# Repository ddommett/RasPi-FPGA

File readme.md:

# RasPi_FPGA

RasPi_FPGA is a master project encapsulating all of my open source and open hardware projects that connect a FPGA (Lattice ice40HX4K and ECP5) to the Raspberry Pi 4 and Raspberry Pi 5 for real-time (relatively high-speed) data transfer via GPIO.

[Part 1](./Part1/readme.md) Raspberry Pi 4 with Lattice ice40HX4K FPGA using GPIO.

[Part 2](./Part2/readme.md) Raspberry Pi 5 with Lattice ECP5 FPGA using HDMI and CSI2.

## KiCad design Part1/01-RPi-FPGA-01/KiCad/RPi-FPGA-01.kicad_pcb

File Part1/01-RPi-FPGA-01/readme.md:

# RPi-FPGA-01

<div align="center">
  
</div>

<p>
The RPi-FPGA-01 is a fully open source (GPLv3) hardware design. It contains a Lattice ice40HX4K FPGA and a 40-pin header. It is intended to plug into a Raspberry Pi. It contains 56 I/O to the "outside" world via three headers and connects to all 28 GPIO pins of the Raspberry Pi. It is a 4-layer PCB with components on one side.

Aside from a few JMP inputs and LEDs, it is intended to be a simple board. It is just an FPGA designed to sit between a Raspberry Pi and any other circuit. The I/O lines are completely unprotected so static electricity from a human touching any of the IO could ruin the FPGA; please be careful.

(The IceZero was not ideal for my purposes. It had extra components, and GPIO lines were organized inefficiently for what I had in mind. Therefore I designed my own PCB.)
</p>

The [KiCad](https://github/ddommett/RasPi_FPGA/03-RPi-FPGA-01/KiCad) folder contains the KiCad project, schematic, and PCB layout design. 

The [gerbers](https://github/ddommett/RasPi_FPGA/03-RPi-FPGA-01/KiCad/gerbers) subfolder contains the gerber files for manufacture. 

The [production](https://github/ddommett/RasPi_FPGA/03-RPi-FPGA-01/KiCad/production) subfolder contains extra files useful for manufacture. I had [JLCPCB](https://jlcpcb.com/) manufacture the PCBs, supply the components, and assemble the board.

RPi-FPGA-01.csv contains a bill of materials for all components on the RPi-FPGA-01 that is in the correct format to upload to JLCPCB during the ordering process. 

jlcpcb-all-cpl.csv contains a list of positions and rotations for all components, uploadable to JLCPCB during their ordering process that enables their pick-and-place machine to perform the assembly.

## License
The RPi-FPGA-01 is an open source project licensed under GPLv3.  Please see the included LICENSE file for details.  If you do wish to distribute boards derived from this open source hardware project then you must also release the source files for the boards under GPLv3.  You are free to do this, but please improve upon the original design and provide a tangible benefit for users of the board.

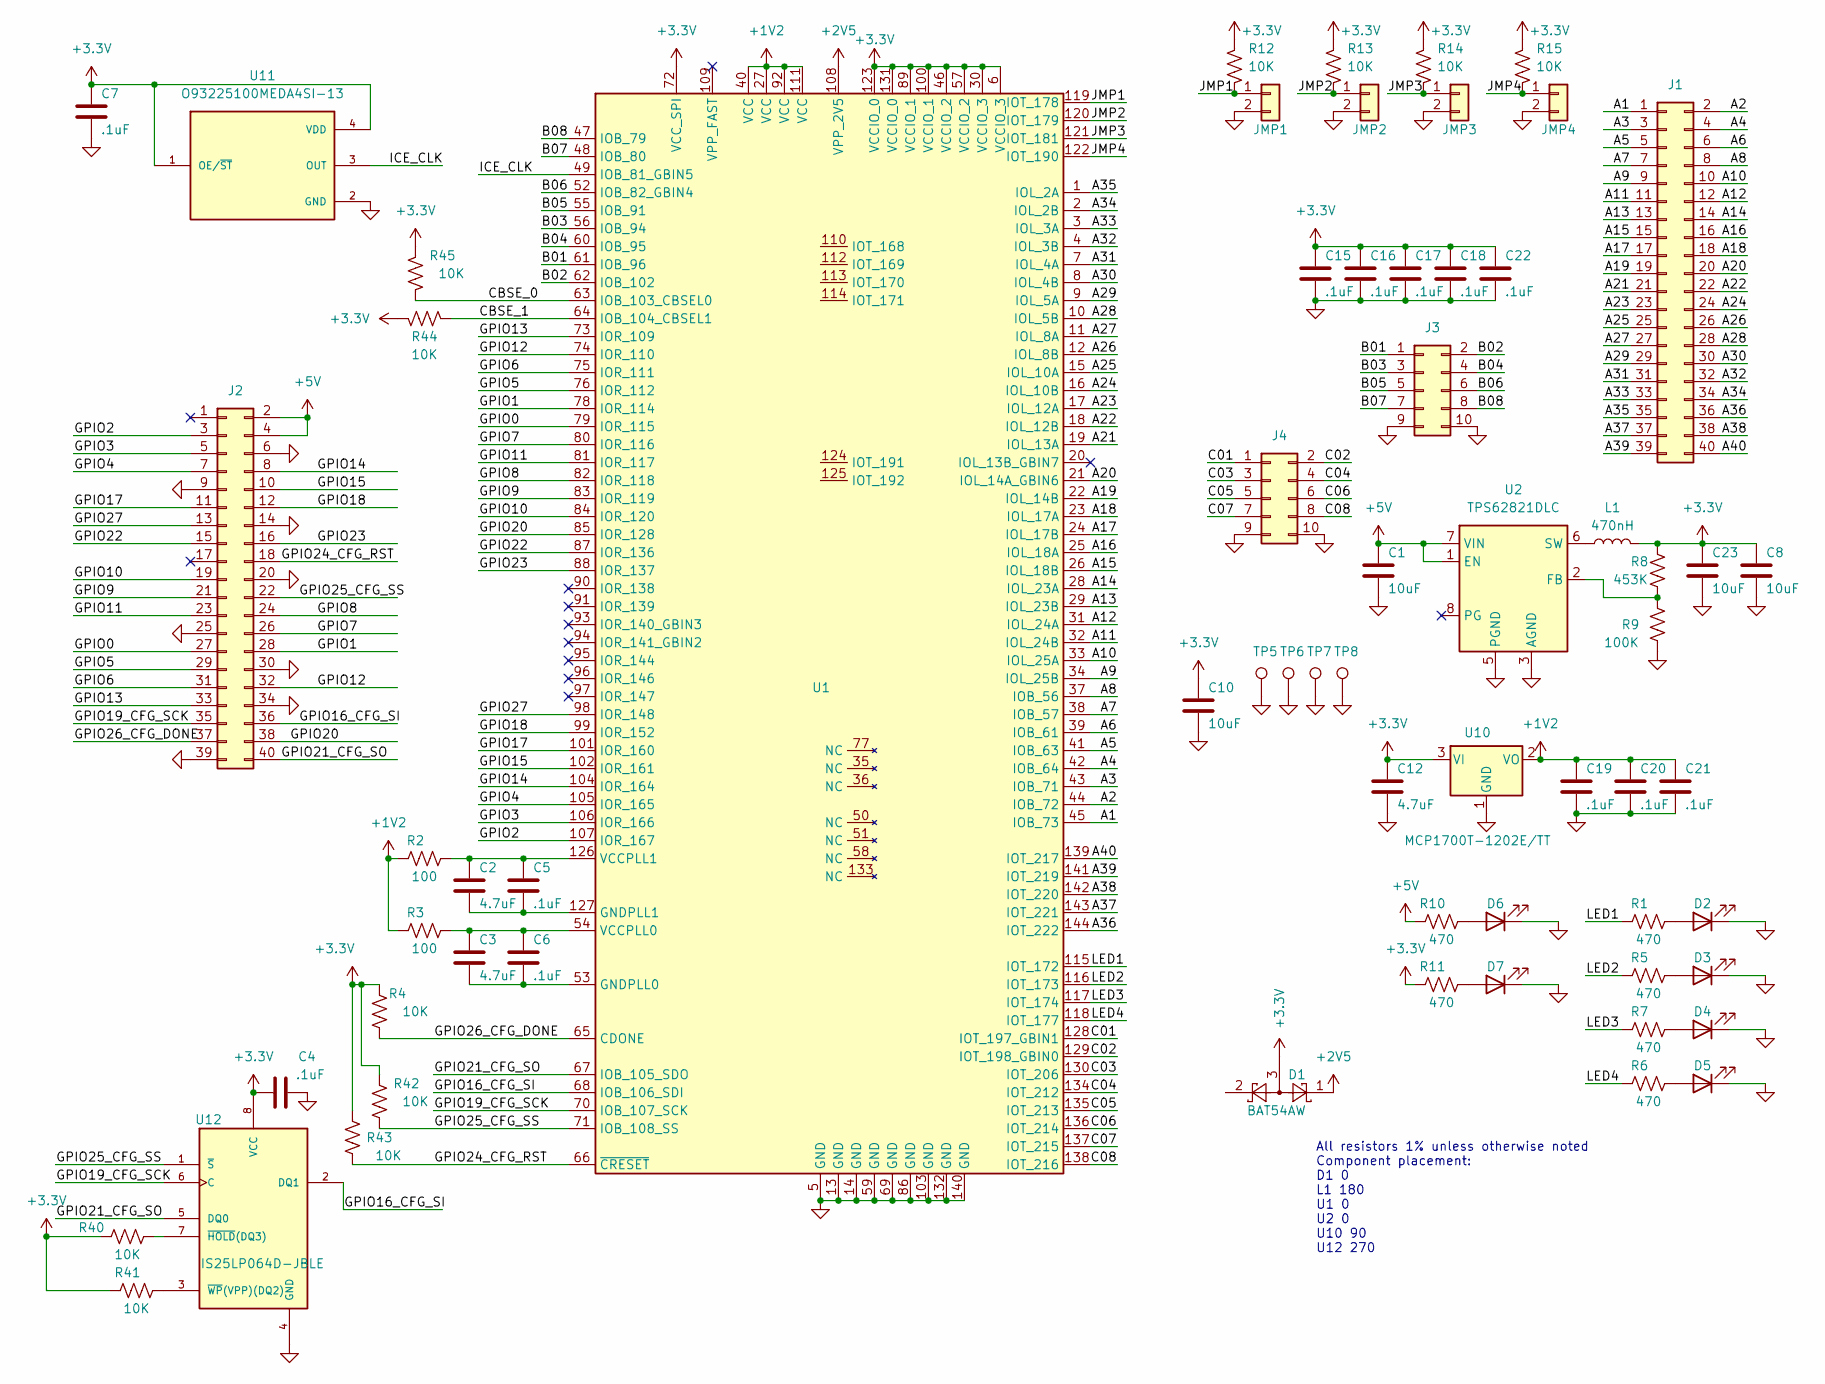
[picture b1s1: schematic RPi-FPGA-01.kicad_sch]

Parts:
C1, C8, C10, C23: 10uF; C_0805_2012Metric; LCSC Part C17024
C2, C3, C12: 4.7uF; C_0402_1005Metric; LCSC Part C307423
C4, C5, C6, C7, C15, C16, C17, C18, C19, C20, C21, C22: .1uF; C_0402_1005Metric; LCSC Part C880603
D1: BAT54AW; SOT-323_SC-70; LCSC Part C22466374
D2, D3, D4, D5: LED-RED; LED_0603_1608Metric; LCSC Part C2286
D6, D7: LED; LED_0603_1608Metric; LCSC Part C12624
J1, J2: Conn_02x20_Odd_Even; PinHeader_2x20_P2.54mm_Vertical
J3, J4: Conn_02x05_Odd_Even; PinHeader_2x05_P2.54mm_Vertical
JMP1, JMP2, JMP3, JMP4: Conn_01x02; PinHeader_1x02_P2.54mm_Vertical
L1: 470nH; XFL4015-471; LCSC Part C18221164
R1, R5, R6, R7, R10, R11: 470; R_0402_1005Metric; LCSC Part C25117
R2, R3: 100; R_0402_1005Metric; LCSC Part C25076
R4, R12, R13, R14, R15, R40, R41, R42, R43, R44, R45: 10K; R_0402_1005Metric; LCSC Part C25744
R8: 453K; R_0402_1005Metric; LCSC Part C27009
R9: 100K; R_0402_1005Metric; LCSC Part C25530
TP5, TP6, TP7, TP8: TestPoint; TestPoint_THTPad_D2.0mm_Drill1.0mm; JLCPCB BOM false
U1: TQFP-144_20x20mm_P0.5mm; LCSC Part C1521989
U2: TPS62821DLC; Texas_VSON-HR-8_1.5x2mm_P0.5mm; LCSC Part C469860
U10: MCP1700T-1202E/TT; SOT-23; LCSC Part C144202
U11: O93225100MEDA4SI-13; SMD3225; PARTREV 1.11; LCSC Part C496694
U12: IS25LP064D-JBLE; SO-8_5.3x6.2mm_P1.27mm; LCSC Part C4943337

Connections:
+1V2: C19.1, C20.1, C21.1, R2.1, R3.1, U1.27 (VCC), U1.40 (VCC), U1.92 (VCC), U1.111 (VCC), U10.2 (VO)
+2V5: D1.1, U1.108 (VPP_2V5)
+3.3V: C4.1, C7.1, C8.1, C10.1, C12.1, C15.1, C16.1, C17.1, C18.1, C22.1, C23.1, D1.3, L1.1, R4.2, R8.2, R11.1, R12.1, R13.1, R14.1, R15.1, R40.1, R41.1, R42.2, R43.2, R44.1, R45.1, U1.6 (VCCIO_3), U1.30 (VCCIO_3), U1.46 (VCCIO_2), U1.57 (VCCIO_2), U1.72 (VCC_SPI), U1.89 (VCCIO_1), U1.100 (VCCIO_1), U1.123 (VCCIO_0), U1.131 (VCCIO_0), U10.3 (VI), U11.1 (OE/~ST), U11.4 (VDD), U12.8 (VCC)
+5V: C1.1, J2.2, J2.4, R10.1, U2.1 (EN), U2.7 (VIN)
/A1: J1.1, U1.45 (IOB_73)
/A2: J1.2, U1.44 (IOB_72)
/A3: J1.3, U1.43 (IOB_71)
/A4: J1.4, U1.42 (IOB_64)
/A5: J1.5, U1.41 (IOB_63)
/A6: J1.6, U1.39 (IOB_61)
/A7: J1.7, U1.38 (IOB_57)
/A8: J1.8, U1.37 (IOB_56)
/A9: J1.9, U1.34 (IOL_25B)
/A10: J1.10, U1.33 (IOL_25A)
/A11: J1.11, U1.32 (IOL_24B)
/A12: J1.12, U1.31 (IOL_24A)
/A13: J1.13, U1.29 (IOL_23B)
/A14: J1.14, U1.28 (IOL_23A)
/A15: J1.15, U1.26 (IOL_18B)
/A16: J1.16, U1.25 (IOL_18A)
/A17: J1.17, U1.24 (IOL_17B)
/A18: J1.18, U1.23 (IOL_17A)
/A19: J1.19, U1.22 (IOL_14B)
/A20: J1.20, U1.21 (IOL_14A_GBIN6)
/A21: J1.21, U1.19 (IOL_13A)
/A22: J1.22, U1.18 (IOL_12B)
/A23: J1.23, U1.17 (IOL_12A)
/A24: J1.24, U1.16 (IOL_10B)
/A25: J1.25, U1.15 (IOL_10A)
/A26: J1.26, U1.12 (IOL_8B)
/A27: J1.27, U1.11 (IOL_8A)
/A28: J1.28, U1.10 (IOL_5B)
/A29: J1.29, U1.9 (IOL_5A)
/A30: J1.30, U1.8 (IOL_4B)
/A31: J1.31, U1.7 (IOL_4A)
/A32: J1.32, U1.4 (IOL_3B)
/A33: J1.33, U1.3 (IOL_3A)
/A34: J1.34, U1.2 (IOL_2B)
/A35: J1.35, U1.1 (IOL_2A)
/A36: J1.36, U1.144 (IOT_222)
/A37: J1.37, U1.143 (IOT_221)
/A38: J1.38, U1.142 (IOT_220)
/A39: J1.39, U1.141 (IOT_219)
/A40: J1.40, U1.139 (IOT_217)
/B01: J3.1, U1.61 (IOB_96)
/B02: J3.2, U1.62 (IOB_102)
/B03: J3.3, U1.56 (IOB_94)
/B04: J3.4, U1.60 (IOB_95)
/B05: J3.5, U1.55 (IOB_91)
/B06: J3.6, U1.52 (IOB_82_GBIN4)
/B07: J3.7, U1.48 (IOB_80)
/B08: J3.8, U1.47 (IOB_79)
/C01: J4.1, U1.128 (IOT_197_GBIN1)
/C02: J4.2, U1.129 (IOT_198_GBIN0)
/C03: J4.3, U1.130 (IOT_206)
/C04: J4.4, U1.134 (IOT_212)
/C05: J4.5, U1.135 (IOT_213)
/C06: J4.6, U1.136 (IOT_214)
/C07: J4.7, U1.137 (IOT_215)
/C08: J4.8, U1.138 (IOT_216)
/CBSE_0: R45.2, U1.63 (IOB_103_CBSEL0)
/CBSE_1: R44.2, U1.64 (IOB_104_CBSEL1)
/GPIO0: J2.27, U1.79 (IOR_115)
/GPIO1: J2.28, U1.78 (IOR_114)
/GPIO2: J2.3, U1.107 (IOR_167)
/GPIO3: J2.5, U1.106 (IOR_166)
/GPIO4: J2.7, U1.105 (IOR_165)
/GPIO5: J2.29, U1.76 (IOR_112)
/GPIO6: J2.31, U1.75 (IOR_111)
/GPIO7: J2.26, U1.80 (IOR_116)
/GPIO8: J2.24, U1.82 (IOR_118)
/GPIO9: J2.21, U1.83 (IOR_119)
/GPIO10: J2.19, U1.84 (IOR_120)
/GPIO11: J2.23, U1.81 (IOR_117)
/GPIO12: J2.32, U1.74 (IOR_110)
/GPIO13: J2.33, U1.73 (IOR_109)
/GPIO14: J2.8, U1.104 (IOR_164)
/GPIO15: J2.10, U1.102 (IOR_161)
/GPIO16_CFG_SI: J2.36, U1.68 (IOB_106_SDI), U12.2 (DQ1)
/GPIO17: J2.11, U1.101 (IOR_160)
/GPIO18: J2.12, U1.99 (IOR_152)
/GPIO19_CFG_SCK: J2.35, U1.70 (IOB_107_SCK), U12.6 (C)
/GPIO20: J2.38, U1.85 (IOR_128)
/GPIO21_CFG_SO: J2.40, U1.67 (IOB_105_SDO), U12.5 (DQ0)
/GPIO22: J2.15, U1.87 (IOR_136)
/GPIO23: J2.16, U1.88 (IOR_137)
/GPIO24_CFG_RST: J2.18, R43.1, U1.66 (~CRESET)
/GPIO25_CFG_SS: J2.22, R42.1, U1.71 (IOB_108_SS), U12.1 (~S)
/GPIO26_CFG_DONE: J2.37, R4.1, U1.65 (CDONE)
/GPIO27: J2.13, U1.98 (IOR_148)
/ICE_CLK: U1.49 (IOB_81_GBIN5), U11.3 (OUT)
/JMP1: JMP1.1, R12.2, U1.119 (IOT_178)
/JMP2: JMP2.1, R13.2, U1.120 (IOT_179)
/JMP3: JMP3.1, R14.2, U1.121 (IOT_181)
/JMP4: JMP4.1, R15.2, U1.122 (IOT_190)
/LED1: R1.1, U1.115 (IOT_172)
/LED2: R5.1, U1.116 (IOT_173)
/LED3: R7.1, U1.117 (IOT_174)
/LED4: R6.1, U1.118 (IOT_177)
GND: C1.2, C4.2, C7.2, C8.2, C10.2, C12.2, C15.2, C16.2, C17.2, C18.2, C19.2, C20.2, C21.2, C22.2, C23.2, D2.1 (K), D3.1 (K), D4.1 (K), D5.1 (K), D6.1 (K), D7.1 (K), J2.6, J2.9, J2.14, J2.20, J2.25, J2.30, J2.34, J2.39, J3.9, J3.10, J4.9, J4.10, JMP1.2, JMP2.2, JMP3.2, JMP4.2, R9.1, TP5.1, TP6.1, TP7.1, TP8.1, U1.5 (GND), U1.13 (GND), U1.14 (GND), U1.59 (GND), U1.69 (GND), U1.86 (GND), U1.103 (GND), U1.132 (GND), U1.140 (GND), U2.3 (AGND), U2.5 (PGND), U10.1 (GND), U11.2 (GND), U12.4 (GND)
unnamed: D2.2 (A), R1.2
unnamed: D3.2 (A), R5.2
unnamed: D4.2 (A), R7.2
unnamed: D5.2 (A), R6.2
unnamed: D6.2 (A), R10.2
unnamed: D7.2 (A), R11.2
unnamed: C3.2, C6.2, U1.53 (GNDPLL0)
unnamed: C2.2, C5.2, U1.127 (GNDPLL1)
unnamed: C3.1, C6.1, R3.2, U1.54 (VCCPLL0)
unnamed: C2.1, C5.1, R2.2, U1.126 (VCCPLL1)
unnamed: R8.1, R9.2, U2.2 (FB)
unnamed: L1.2, U2.6 (SW)
unnamed: R40.2, U12.7 (~HOLD(DQ3))
unnamed: R41.2, U12.3 (~WP(VPP)(DQ2))

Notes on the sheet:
All resistors 1% unless otherwise noted Component placement: D1 0 L1 180 U1 0 U2 0 U10 90 U12 270

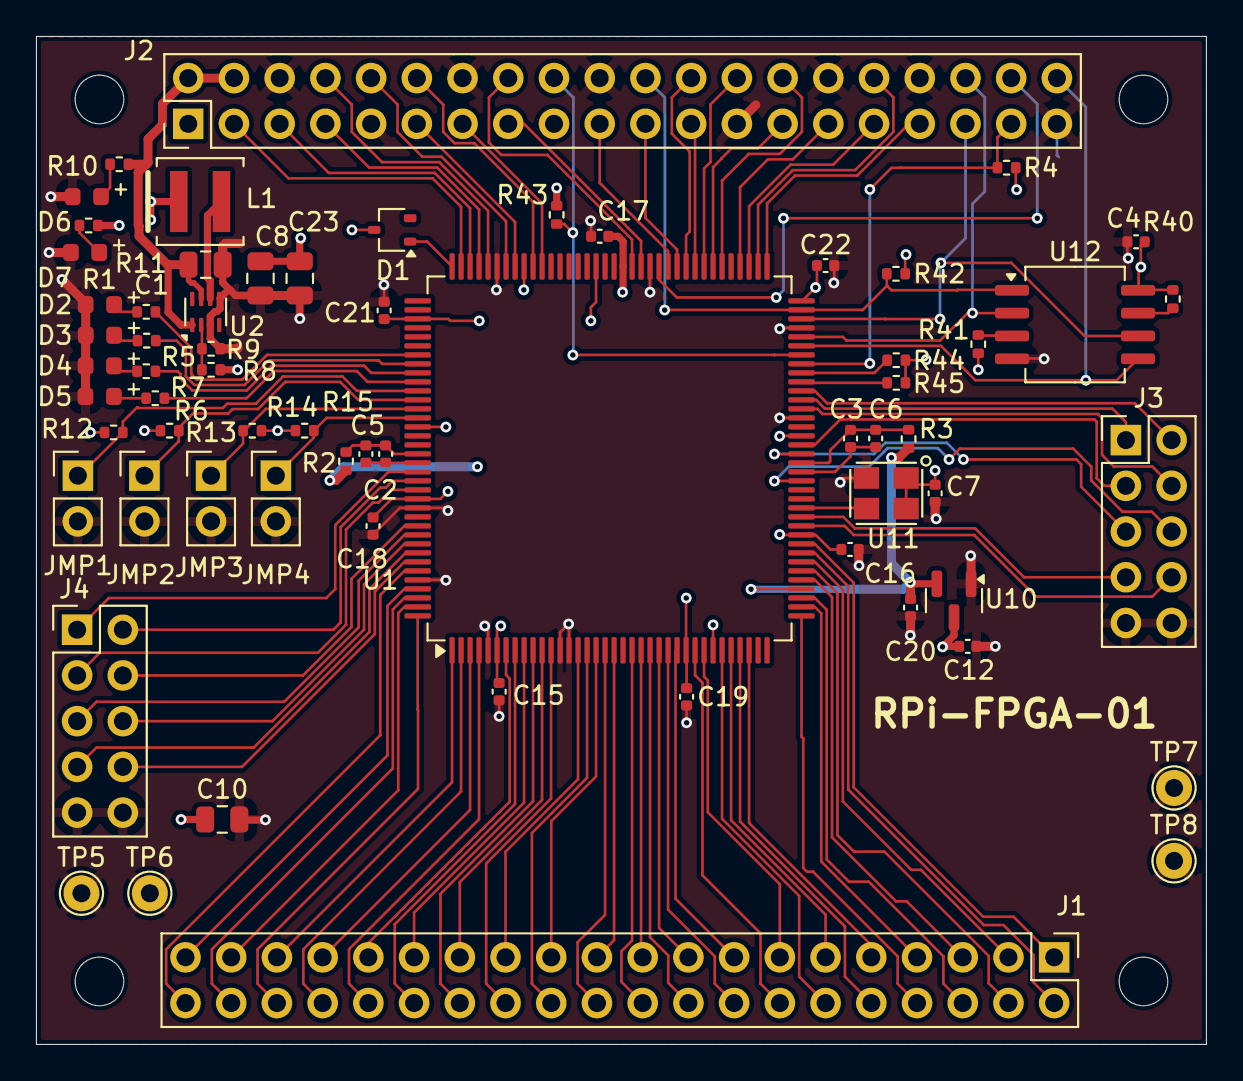
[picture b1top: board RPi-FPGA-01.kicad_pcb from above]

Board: 4 copper layers, 65.0 x 56.0 mm, 65 parts (0 on the bottom side), 114 nets.

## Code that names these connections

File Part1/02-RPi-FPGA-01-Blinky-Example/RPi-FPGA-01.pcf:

set_io clk_100mhz 49

set_io led1 115
set_io led2 116
set_io led3 117
set_io led4 118
